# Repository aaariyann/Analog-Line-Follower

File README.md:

Analog Line Follower

A line follower where the steering loop has no microcontroller in it. Ten reflective sensors go in, two motor PWM signals come out, and everything in between is op-amps, resistors and one comparator.

Status: schematic complete in KiCad. Not simulated or fabricated yet. This repo will be updated as that happens.

Why analog

Most line followers read sensors with an ADC, run a PID loop in code and write PWM. I wanted to see how far the same idea goes when the loop is built from circuits you can probe with a scope. There’s no sampling delay or loop rate to tune around, and every signal in the controller is a voltage you can look at. It also makes the PID terms very direct: Kp, Ki and Kd are trimmer pots on the board.

How it works

Sensing. Ten QRE1113 reflectance sensors, each buffered by an op-amp so the later stages don’t load them.
Position error. The right-side signals are inverted around a 2.5 V reference, then all ten are summed with weighted resistors (100k down to 20k). Sensors farther from center pull harder. A pot sets overall gain and another trims the center offset.
PID. Separate P, I and D op-amp stages feed a summer. The integral stage is built but left unpopulated by default, so the first version runs as PD.
Speed and steering. A base-speed pot is added to the PID output for one motor and subtracted for the other.
PWM. A triangle oscillator around 5 kHz is compared against each motor’s duty voltage by an LM339.
Drive. Two AO3400A MOSFETs switch the motors low-side, with flyback diodes.
Power. An AP63205 steps 12 V down to 5 V. A buffered divider provides the 2.5 V reference.

Test points are placed on the key signals (error, P, I, D, PID output, triangle, duty, PWM) so each stage can be checked on its own.

Parts

10 × QRE1113GR sensors
7 × MCP6004 quad op-amps
1 × LM339 comparator
1 × AP63205 buck regulator
2 × AO3400A MOSFETs, 2 × SS14 diodes
Trimmers for Kp, Ki, Kd, gain, offset and base speed

What I want to check next

Simulate the PID response and the triangle/PWM stage.
Confirm the LM339 input range is comfortable with the triangle peak.
Check PWM edge speed at the gates.
Add reverse or braking, and handling for junctions and dashed lines, if the base design works well.

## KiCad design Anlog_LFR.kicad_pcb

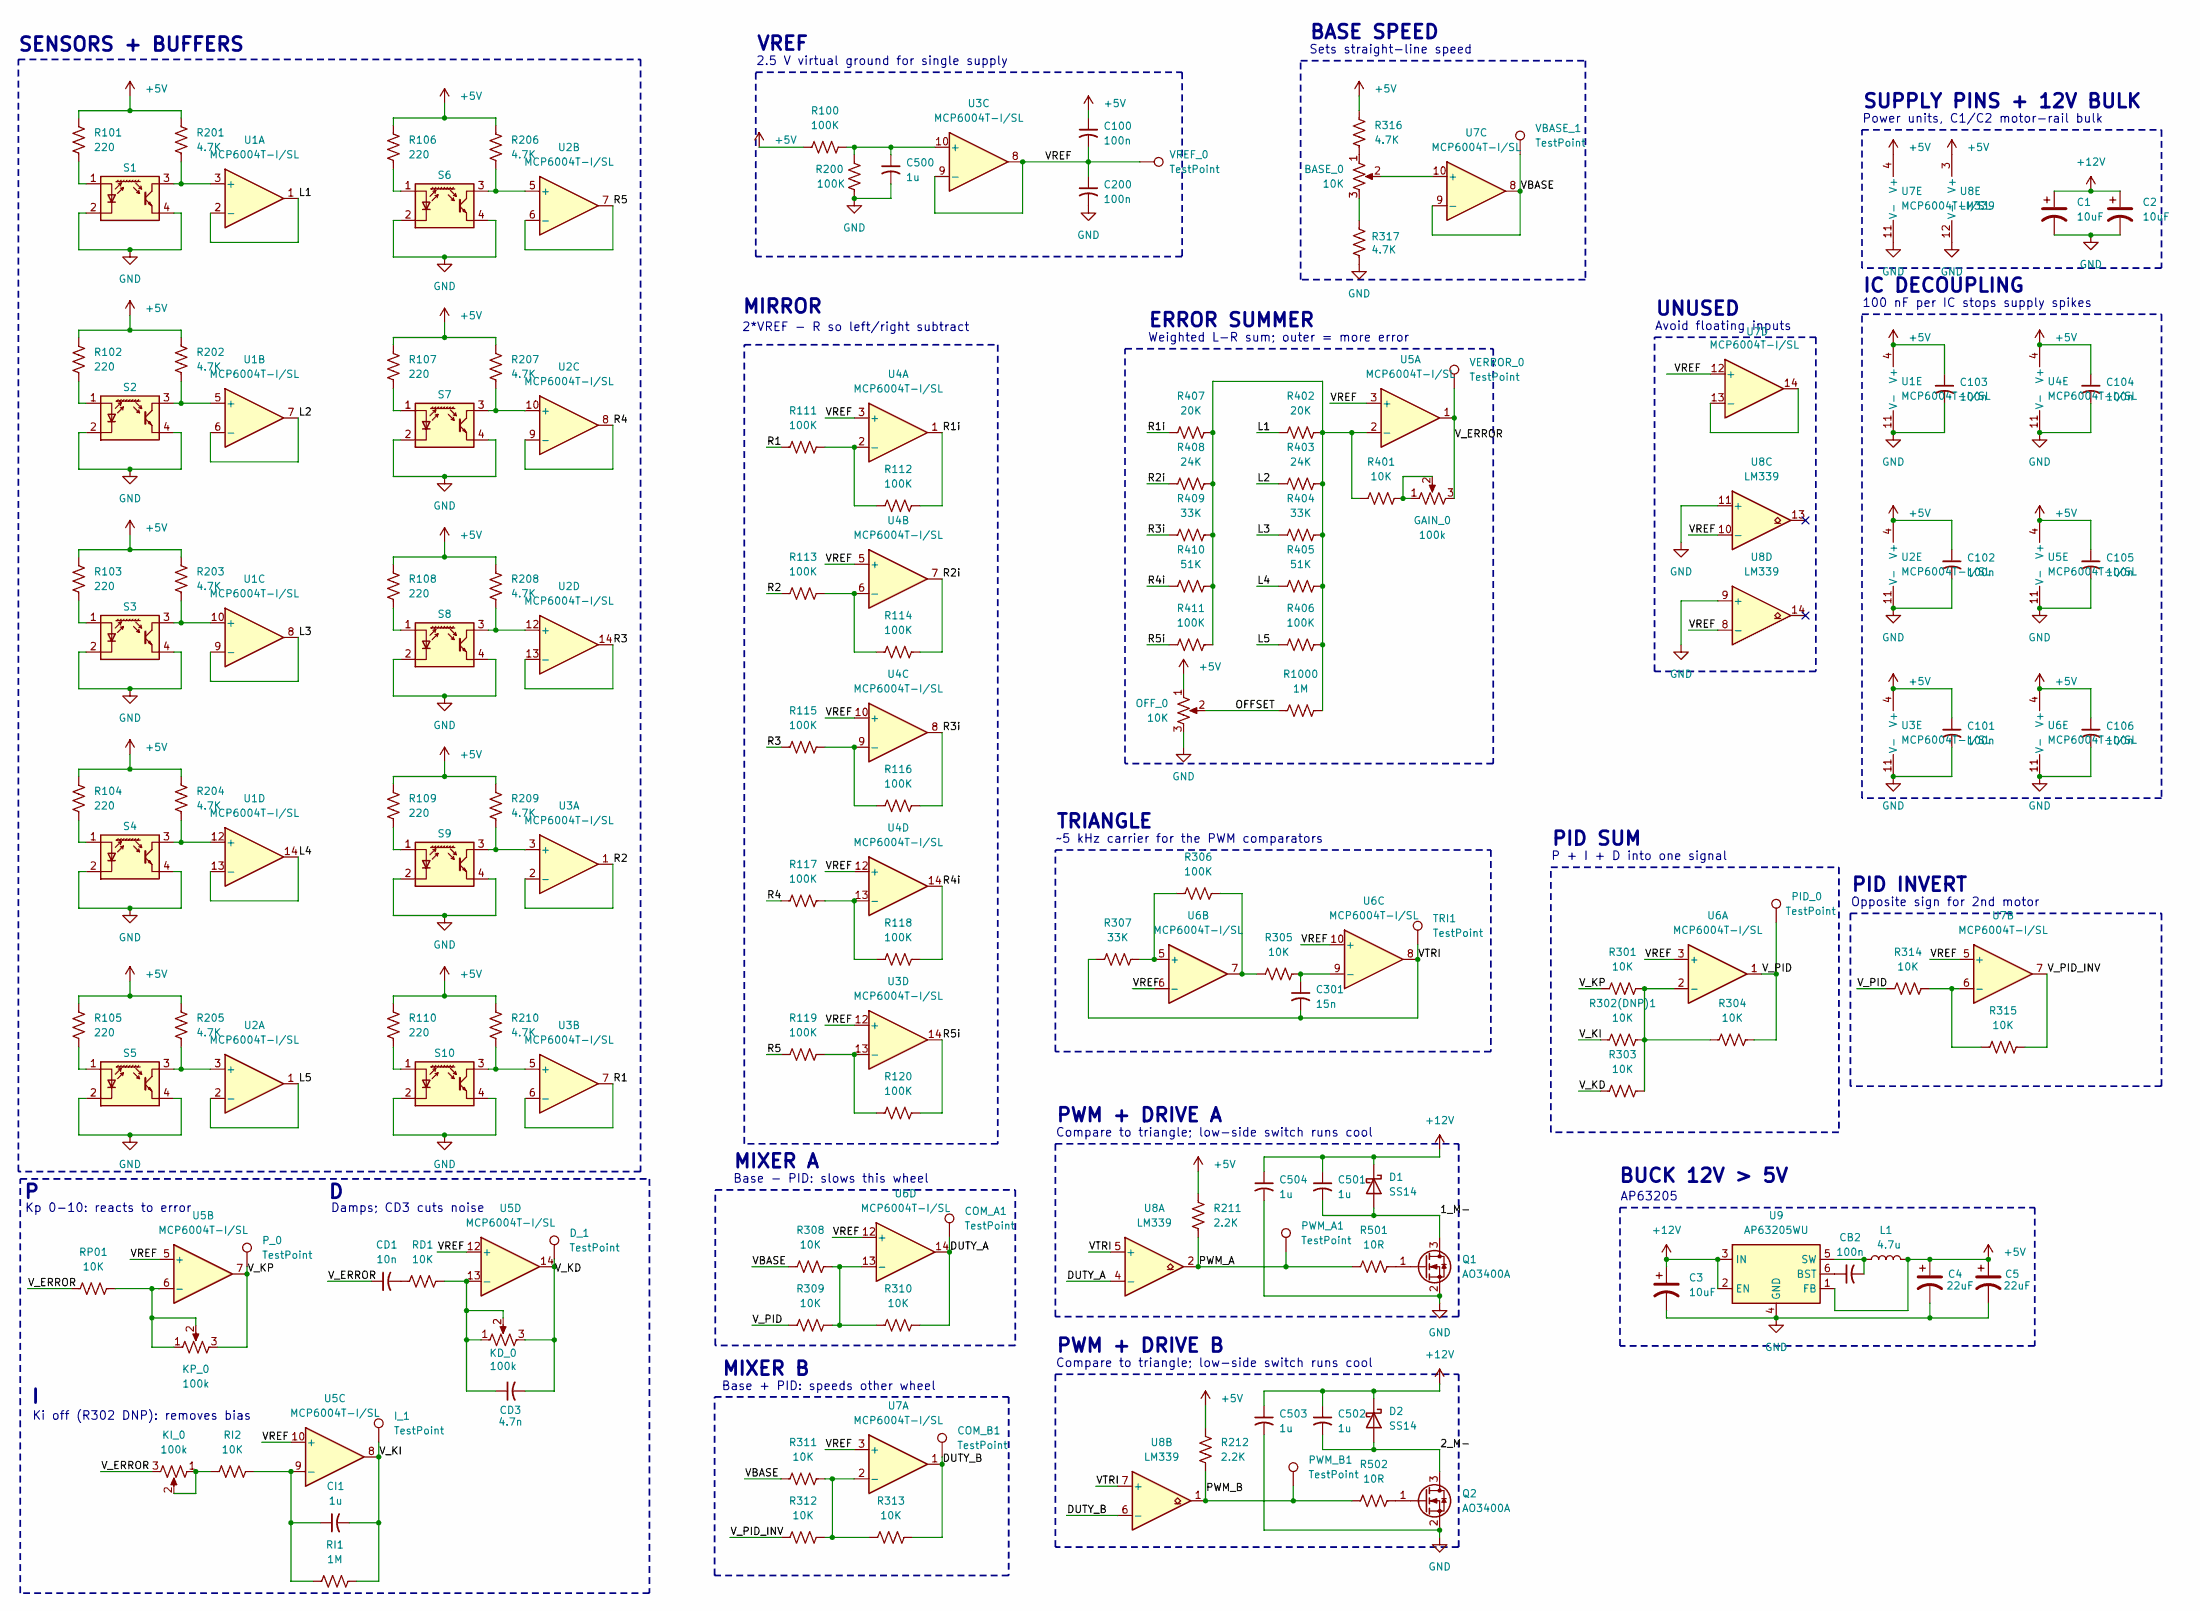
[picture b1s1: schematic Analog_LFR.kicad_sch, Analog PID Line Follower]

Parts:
BASE_0: 10K; Potentiometer_Bourns_3224W_Vertical
C1, C2: 10uF; CP_Elec_5x5.4
C3: 10uF; C_1206_3216Metric_Pad1.33x1.80mm_HandSolder
C4, C5: 22uF; C_1206_3216Metric_Pad1.33x1.80mm_HandSolder
C100, C101, C102, C103, C104, C105, C106, C200: 100n; C_1206_3216Metric_Pad1.33x1.80mm_HandSolder
C301: 15n; C_0805_2012Metric_Pad1.18x1.45mm_HandSolder
C500, C501, C502, C503, C504: 1u; C_0805_2012Metric_Pad1.18x1.45mm_HandSolder
CB2: 100n; C_1206_3216Metric_Pad1.33x1.80mm_HandSolder
CD1: 10n; C_1206_3216Metric_Pad1.33x1.80mm_HandSolder
CD3: 4.7n; C_1206_3216Metric_Pad1.33x1.80mm_HandSolder
CI1: 1u; C_0805_2012Metric_Pad1.18x1.45mm_HandSolder
COM_A1: TestPoint; TestPoint_Pad_D2.0mm
COM_B1: TestPoint; TestPoint_Pad_D2.0mm
D1, D2: SS14; D_SMA
D_1: TestPoint; TestPoint_Pad_D2.0mm
GAIN_0: 100k; Potentiometer_Bourns_3224W_Vertical
I_1: TestPoint; TestPoint_Pad_D2.0mm
KD_0: 100k; Potentiometer_Bourns_3224W_Vertical
KI_0: 100k; Potentiometer_Bourns_3224W_Vertical
KP_0: 100k; Potentiometer_Bourns_3224W_Vertical
L1: 4.7u; L_7.3x7.3_H3.5
OFF_0: 10K; Potentiometer_Bourns_3224W_Vertical
PID_0: TestPoint; TestPoint_Pad_D2.0mm
PWM_A1: TestPoint; TestPoint_Pad_D2.0mm
PWM_B1: TestPoint; TestPoint_Pad_D2.0mm
P_0: TestPoint; TestPoint_Pad_D2.0mm
Q1, Q2: AO3400A; SOT-23-3
R100, R111, R112, R113, R114, R115, R116, R117, R118, R119, R120, R200, R306, R406, R411: 100K; R_1206_3216Metric_Pad1.30x1.75mm_HandSolder
R101, R102, R103, R104, R105, R106, R107, R108, R109, R110: 220; R_1206_3216Metric_Pad1.30x1.75mm_HandSolder
R201, R202, R203, R204, R205, R206, R207, R208, R209, R210, R316, R317: 4.7K; R_1206_3216Metric_Pad1.30x1.75mm_HandSolder
R211, R212: 2.2K; R_1206_3216Metric_Pad1.30x1.75mm_HandSolder
R301, R302(DNP)1, R303, R304, R305, R308, R309, R310, R311, R312, R313, R314, R315, R401: 10K; R_1206_3216Metric_Pad1.30x1.75mm_HandSolder
R307, R404, R409: 33K; R_1206_3216Metric_Pad1.30x1.75mm_HandSolder
R402, R407: 20K; R_1206_3216Metric_Pad1.30x1.75mm_HandSolder
R403, R408: 24K; R_1206_3216Metric_Pad1.30x1.75mm_HandSolder
R405, R410: 51K; R_1206_3216Metric_Pad1.30x1.75mm_HandSolder
R501, R502: 10R; R_1206_3216Metric_Pad1.30x1.75mm_HandSolder
R1000: 1M; R_1206_3216Metric_Pad1.30x1.75mm_HandSolder
RD1: 10K; R_1206_3216Metric_Pad1.30x1.75mm_HandSolder
RI1: 1M; R_1206_3216Metric_Pad1.30x1.75mm_HandSolder
RI2: 10K; R_1206_3216Metric_Pad1.30x1.75mm_HandSolder
RP01: 10K; R_1206_3216Metric_Pad1.30x1.75mm_HandSolder
S1, S2, S3, S4, S5, S6, S7, S8, S9, S10: QRE1113GR; OnSemi_CASE100CY
TRI1: TestPoint; TestPoint_Pad_D2.0mm
U1, U2, U3, U4, U5, U6, U7: MCP6004T-I/SL; SOIC-14_3.9x8.7mm_P1.27mm
U8: LM339; SOIC-14_3.9x8.7mm_P1.27mm
U9: AP63205WU; TSOT-23-6
VBASE_1: TestPoint; TestPoint_Pad_D2.0mm
VERROR_0: TestPoint; TestPoint_Pad_D2.0mm
VREF_0: TestPoint; TestPoint_Pad_D2.0mm

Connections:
+5V: C4.1, C5.1, C100.1, C101.1, C102.1, C103.1, C104.1, C105.1, C106.1, L1.2, OFF_0.1, R100.1, R101.1, R102.1, R103.1, R104.1, R105.1, R106.1, R107.1, R108.1, R109.1, R110.1, R201.2, R202.2, R203.2, R204.2, R205.2, R206.2, R207.2, R208.2, R209.2, R210.2, R211.2, R212.2, R316.2, U1.4 (V+), U2.4 (V+), U3.4 (V+), U4.4 (V+), U5.4 (V+), U6.4 (V+), U7.4 (V+), U8.3 (V+), U9.1 (FB)
+12V: C1.1, C2.1, C3.1, C501.1, C502.1, C503.1, C504.1, D1.1 (K), D2.1 (K), U9.2 (EN), U9.3 (IN)
/1_M-: C501.2, D1.2 (A), Q1.3 (D)
/2_M-: C502.2, D2.2 (A), Q2.3 (D)
/DUTY_A: COM_A1.1 (1_1), R310.2, U6.14, U8.4 (-)
/DUTY_B: COM_B1.1 (1_1), R313.2, U7.1, U8.6 (-)
/L1: R402.1, U1.1, U1.2 (-)
/L2: R403.1, U1.6 (-), U1.7
/L3: R404.1, U1.8, U1.9 (-)
/L4: R405.1, U1.13 (-), U1.14
/L5: R406.1, U2.1, U2.2 (-)
/OFFSET: OFF_0.2, R1000.1
/PWM_A: PWM_A1.1 (1_1), R211.1, R501.1, U8.2
/PWM_B: PWM_B1.1 (1_1), R212.1, R502.1, U8.1
/R1: R111.1, U3.6 (-), U3.7
/R1i: R112.2, R407.1, U4.1
/R2: R113.1, U3.1, U3.2 (-)
/R2i: R114.2, R408.1, U4.7
/R3: R115.1, U2.13 (-), U2.14
/R3i: R116.2, R409.1, U4.8
/R4: R117.1, U2.8, U2.9 (-)
/R4i: R118.2, R410.1, U4.14
/R5: R119.1, U2.6 (-), U2.7
/R5i: R120.2, R411.1, U3.14
/VBASE: R308.1, R311.1, U7.8, U7.9 (-), VBASE_1.1 (1_1)
/VREF: C100.2, C200.1, U3.8, U3.9 (-), U3.12 (+), U4.3 (+), U4.5 (+), U4.10 (+), U4.12 (+), U5.3 (+), U5.5 (+), U5.10 (+), U5.12 (+), U6.3 (+), U6.6 (-), U6.10 (+), U6.12 (+), U7.3 (+), U7.5 (+), U7.12 (+), U8.8 (-), U8.10 (-), VREF_0.1 (1_1)
/VTRI: C301.2, R307.1, TRI1.1 (1_1), U6.8, U8.5 (+), U8.7 (+)
/V_ERROR: CD1.1, GAIN_0.3, KI_0.3, RP01.1, U5.1, VERROR_0.1 (1_1)
/V_KD: CD3.2, D_1.1 (1_1), KD_0.3, R303.1, U5.14
/V_KI: CI1.2, I_1.1 (1_1), R302(DNP)1.1, RI1.2, U5.8
/V_KP: KP_0.3, P_0.1 (1_1), R301.1, U5.7
/V_PID: PID_0.1 (1_1), R304.2, R309.1, R314.1, U6.1
/V_PID_INV: R312.1, R315.2, U7.7
GND: C1.2, C2.2, C3.2, C4.2, C5.2, C101.2, C102.2, C103.2, C104.2, C105.2, C106.2, C200.2, C500.2, C503.2, C504.2, OFF_0.3, Q1.2 (S), Q2.2 (S), R200.2, R317.1, S1.2 (K), S1.4, S2.2 (K), S2.4, S3.2 (K), S3.4, S4.2 (K), S4.4, S5.2 (K), S5.4, S6.2 (K), S6.4, S7.2 (K), S7.4, S8.2 (K), S8.4, S9.2 (K), S9.4, S10.2 (K), S10.4, U1.11 (V-), U2.11 (V-), U3.11 (V-), U4.11 (V-), U5.11 (V-), U6.11 (V-), U7.11 (V-), U8.9 (+), U8.11 (+), U8.12 (V-), U9.4 (GND)
unnamed: BASE_0.1, R316.1
unnamed: BASE_0.3, R317.2
unnamed: CD1.2, RD1.1
unnamed: GAIN_0.1, GAIN_0.2, R401.2
unnamed: KI_0.1, KI_0.2, RI2.1
unnamed: Q1.1 (G), R501.2
unnamed: Q2.1 (G), R502.2
unnamed: R305.1, R306.2, U6.7
unnamed: R101.2, S1.1 (A)
unnamed: R102.2, S2.1 (A)
unnamed: R103.2, S3.1 (A)
unnamed: R104.2, S4.1 (A)
unnamed: R105.2, S5.1 (A)
unnamed: R106.2, S6.1 (A)
unnamed: R107.2, S7.1 (A)
unnamed: R108.2, S8.1 (A)
unnamed: R109.2, S9.1 (A)
unnamed: R110.2, S10.1 (A)
unnamed: R201.1, S1.3, U1.3 (+)
unnamed: R202.1, S2.3, U1.5 (+)
unnamed: R203.1, S3.3, U1.10 (+)
unnamed: R204.1, S4.3, U1.12 (+)
unnamed: R205.1, S5.3, U2.3 (+)
unnamed: R206.1, S6.3, U2.5 (+)
unnamed: R207.1, S7.3, U2.10 (+)
unnamed: R208.1, S8.3, U2.12 (+)
unnamed: R209.1, S9.3, U3.3 (+)
unnamed: R210.1, S10.3, U3.5 (+)
unnamed: C500.1, R100.2, R200.1, U3.10 (+)
unnamed: R119.2, R120.1, U3.13 (-)
unnamed: R111.2, R112.1, U4.2 (-)
unnamed: R113.2, R114.1, U4.6 (-)
unnamed: R115.2, R116.1, U4.9 (-)
unnamed: R117.2, R118.1, U4.13 (-)
unnamed: R401.1, R402.2, R403.2, R404.2, R405.2, R406.2, R407.2, R408.2, R409.2, R410.2, R411.2, R1000.2, U5.2 (-)
unnamed: KP_0.1, KP_0.2, RP01.2, U5.6 (-)
unnamed: CI1.1, RI1.1, RI2.2, U5.9 (-)
unnamed: CD3.1, KD_0.1, KD_0.2, RD1.2, U5.13 (-)
unnamed: R301.2, R302(DNP)1.2, R303.2, R304.1, U6.2 (-)
unnamed: R306.1, R307.2, U6.5 (+)
unnamed: C301.1, R305.2, U6.9 (-)
unnamed: R308.2, R309.2, R310.1, U6.13 (-)
unnamed: R311.2, R312.2, R313.1, U7.2 (-)
unnamed: R314.2, R315.1, U7.6 (-)
unnamed: BASE_0.2, U7.10 (+)
unnamed: U7.13 (-), U7.14
unnamed: CB2.1, U9.6 (BST)
unnamed: CB2.2, L1.1, U9.5 (SW)

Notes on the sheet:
BUCK 12V > 5V
~5 kHz carrier for the PWM comparators
BASE SPEED
IC DECOUPLING
Weighted L-R sum; outer = more error
PWM + DRIVE A
Kp 0-10: reacts to error
VREF
Damps; CD3 cuts noise
Ki off (R302 DNP): removes bias
SUPPLY PINS + 12V BULK
Avoid floating inputs
MIXER A
SENSORS + BUFFERS
Compare to triangle; low-side switch runs cool
PID INVERT
TRIANGLE
Opposite sign for 2nd motor
AP63205
MIXER B
Power units, C1/C2 motor-rail bulk
Base - PID: slows this wheel
Sets straight-line speed
100 nF per IC stops supply spikes
P + I + D into one signal
PID SUM
UNUSED
PWM + DRIVE B
Base + PID: speeds other wheel
MIRROR
ERROR SUMMER
2.5 V virtual ground for single supply
2*VREF - R so left/right subtract

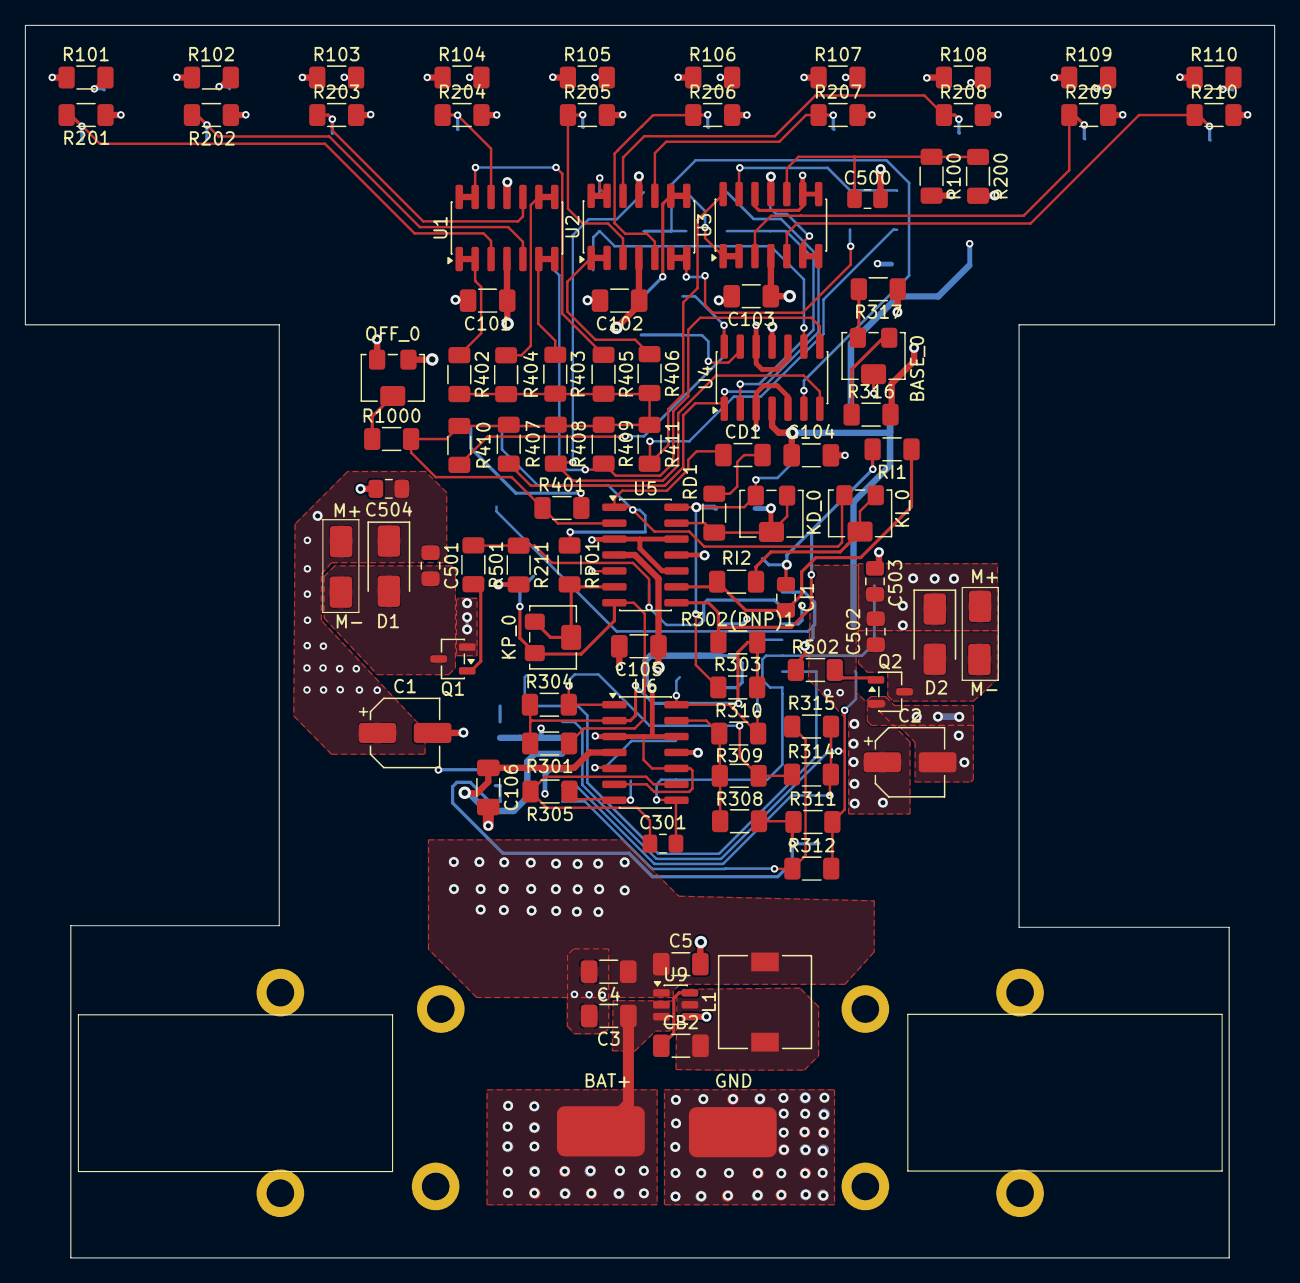
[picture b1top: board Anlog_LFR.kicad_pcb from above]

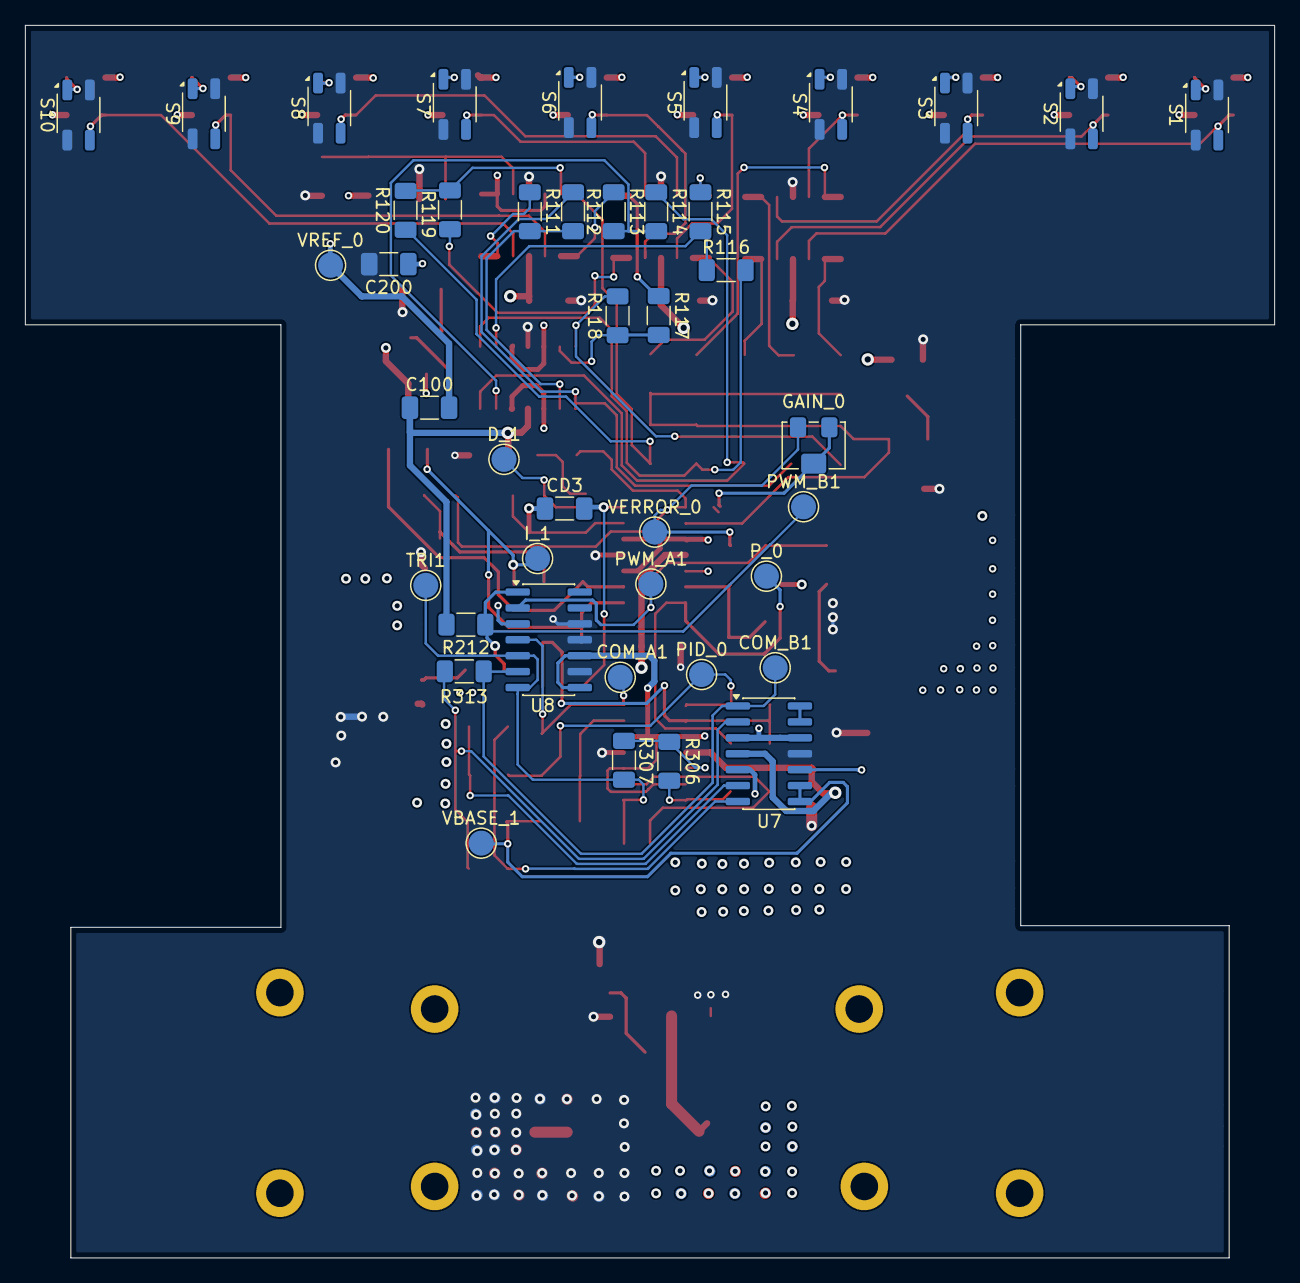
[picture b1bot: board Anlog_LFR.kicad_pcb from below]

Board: 4 copper layers, 99.6 x 98.3 mm, 134 parts (42 on the bottom side), 82 nets.
